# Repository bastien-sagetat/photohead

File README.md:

# Photohead

Photohead is a motorized pan and tilt head on which a camera can be mounted.\

## Initial Concept

## Assembly

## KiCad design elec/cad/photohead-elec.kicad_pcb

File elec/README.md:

# Photohead electronics

The Photohead board aims to drive the stepper motors from PWM signals coming from the Raspberry Pi 5.

To achieve this, two TMC2208 stepper motor drive chips drive two NEMA 17 stepper motors (one for tilting, and one for panning).

🚧: **TODO**: Update overview to show +12V and 3.3V power supplies, GND, and DIR.

**KiCad v8.0 is used throughout this project.**

## Schematic

## Naked board

## Assembled board

## Some therorical stuffs

With microstepping enabled (1/16 microsteps on the TMC2208 chip), and with a step angle of 1.8° on NEMA 17 motors:\
Periods per revolution = (360° / (1.8° / 16)) = 3200 periods\
:arrow_right: 3200 PWM periods are required for the motor to make 1 complete revolution.

If the PWM period is 1 millisecond:\
Full revolution time  = 3200 x 1ms = 3.2s\
:arrow_right: The motor would complete a full revolution in 3.2 seconds.

🚧: **TODO**: Explain Vref calculation.

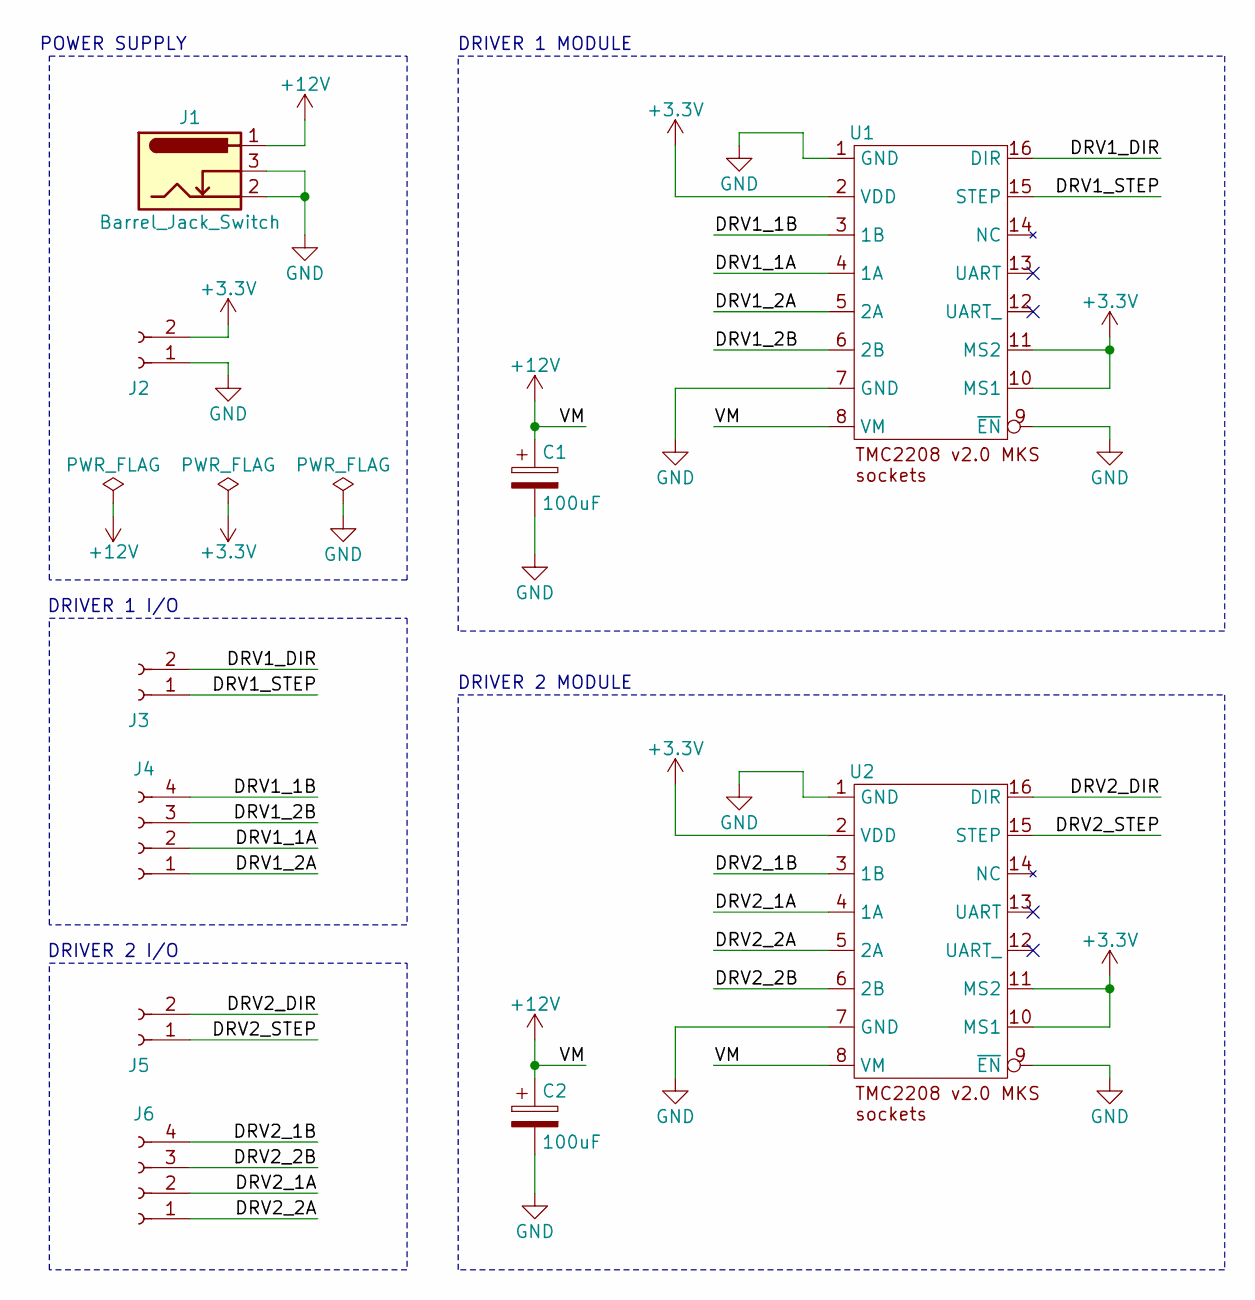
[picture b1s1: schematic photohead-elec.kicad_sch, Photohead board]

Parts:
C1, C2: 100uF
J1: Barrel_Jack_Switch; BarrelJack_Horizontal
J2, J3, J5: Conn_01x02_Socket; PinHeader_1x02_P2.54mm_Vertical
J4, J6: Conn_01x04_Socket; PinHeader_1x04_P2.54mm_Vertical
U1, U2: TMC2208_v2.0_MKS_sockets

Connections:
+3.3V: J2.2, U1.2 (VDD), U1.10 (MS1), U1.11 (MS2), U2.2 (VDD), U2.10 (MS1), U2.11 (MS2)
+12V: C1.1, C2.1, J1.1, U1.8 (VM), U2.8 (VM)
/DRV1_1A: J4.2, U1.4 (1A)
/DRV1_1B: J4.4, U1.3 (1B)
/DRV1_2A: J4.1, U1.5 (2A)
/DRV1_2B: J4.3, U1.6 (2B)
/DRV1_DIR: J3.2, U1.16 (DIR)
/DRV1_STEP: J3.1, U1.15 (STEP)
/DRV2_1A: J6.2, U2.4 (1A)
/DRV2_1B: J6.4, U2.3 (1B)
/DRV2_2A: J6.1, U2.5 (2A)
/DRV2_2B: J6.3, U2.6 (2B)
/DRV2_DIR: J5.2, U2.16 (DIR)
/DRV2_STEP: J5.1, U2.15 (STEP)
GND: C1.2, C2.2, J1.2, J1.3, J2.1, U1.1 (GND), U1.7 (GND), U1.9 (~EN), U2.1 (GND), U2.7 (GND), U2.9 (~EN)

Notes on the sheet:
DRIVER 1 MODULE
POWER SUPPLY
DRIVER 2 I/O
DRIVER 2 MODULE
DRIVER 1 I/O

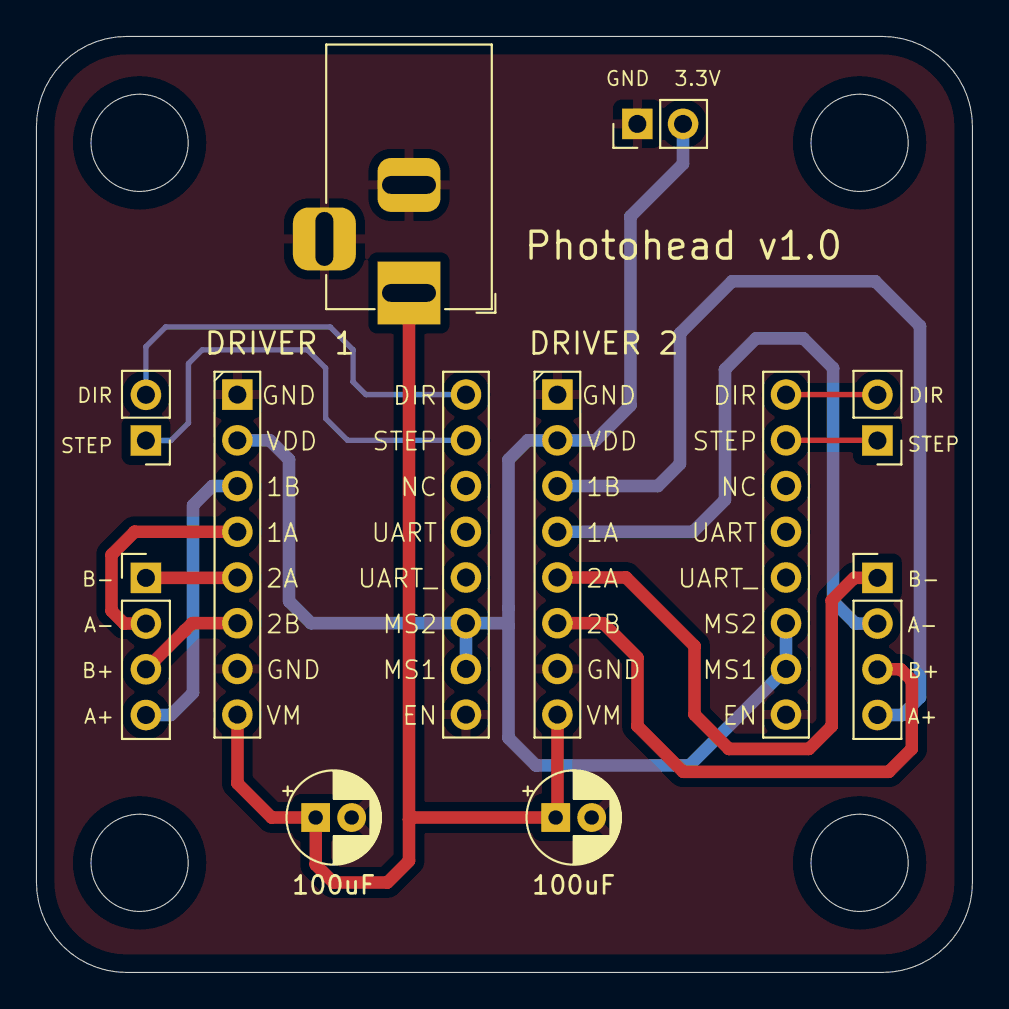
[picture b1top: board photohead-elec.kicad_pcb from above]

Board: 2 copper layers, 52.0 x 52.0 mm, 10 parts (0 on the bottom side), 15 nets.

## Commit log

2023-12-05 Add basic Makefile, main.c, and .gitignore files
2023-12-10 Integrate basic libgphoto2 functions (camera initialization, summary, preview) directly in main.c
2023-12-22 Add camera::File::Mime(), Data() and Size() functions
2023-12-22 Added OpenCV library dependencies
2023-12-22 Convert Camera::File to cv::Mat, and display image in OpenCV window
2023-12-30 Remove Makefile
2023-12-30 Move .h files to src/ folder
2023-12-30 Update main.cpp: remove version infos printing for now
2023-12-30 Update CMakeLists.txt: Link OpenCV library
2023-12-30 Add CMakeLists.txt file
2023-12-30 Update CMakeLists.txt: Link gphoto2 library
2023-12-30 Update CMakeLists.txt: Add compile options/flags
2023-12-30 Add project version printing using CMake template file
2023-12-31 Update CMakeLists.txt: add tensorflow-lite library
2024-01-01 Add model (MobileNetv1-SSD) and model's labels (COCO)
2024-01-01 Update CMakeLists.txt: Copy model and model's labels to build directory
2024-01-01 Integrate object detection directly into main.c (kind of messy but just need a basic integration for now)
2024-01-03 Move model and model's labels to new model/ folder
2024-01-03 Small fix in camera.h
2024-01-06 Add object_detection.cpp/.h source files, and integrate its classes into main.c
2024-01-10 Rework/simplify camera exception
2024-01-10 Add ObjectDetectionException + cosmetics (comments)
2024-01-10 Add PROJECT_NAME to config.h.in template file
2024-01-10 Small ObjectDetector update (score_threshold)
2024-01-10 Update CMakeLists.txt: add comments (cosmetics only)
2024-01-10 Perform continuous image acquisition/processing in while loop
2024-02-02 Rename project (object-detection->owleye)
2024-02-18 Update CMakeLists.txt
    Change required Cmake version
2024-02-24 Add lots of documentation. Rename project
2024-02-26 Apply opaque white background to PNG files
2024-02-26 Resize demo.gif
2024-03-13 Move repository from organization to local repo
2024-03-27 Fix platform - shift the motor downwards - reduce stepper motor bay
2024-03-27 Add platform STL file
2024-04-06 Add tilt head outer bracket FreeCAD file
2024-04-06 Update head outer bracket FreeCAD file
2024-04-06 Add head inner side bracket FreeCAD file
2024-04-06 Add head inner side bracket STL file
2024-04-06 Update head inner side bracket FreeCAD file
2024-04-06 Add head outer bracket STL file
2024-04-06 Add camera mount
2024-04-07 Update README.md: add assembly photo
2024-04-08 Update inner side bracket: remove fillet (was difficult to 3D print)
2024-04-08 Update inner side bracket: remove middle screw holes (2 holes is enough)
2024-04-08 Update inner side bracket: tap the screw holes.
2024-04-08 Update inner side bracket: export STL file
2024-04-09 Update inner side bracket: increase wedge thickness (6mm->8mm)
2024-05-08 Resize camera mount (width set to 134mm)
2024-05-08 Fix typo in config.h.in
2024-05-08 Fix typo in comment
2024-05-08 remove "DLSR" term. Does not have to be a DLSR camera
2024-05-08 Add PWM subproject
2024-05-08 Update requirements.md: Updating "Enabling PWM"
2024-05-08 Update .gitignore (ignore all config.h files)
2026-05-24 REBOOT - Just keeps 3D CAD
    Remove C++ code
    Will use Python app instead
    Remove elec board
    Will use stepper-impulse project instead
2026-05-25 software: bridge: Add blank bridge.py
2026-05-25 software: bridge: Add header to bridge.py
2026-05-25 software: bridge: Basic server
2026-05-25 software: bridge: Add "scan" message type to server
2026-05-26 software: bridge: Add SerialClient and Request classes
2026-06-07 software: bridge: Add bridge script (websocket server)
    Provide a network bridge (websocket),
    to access stepper motor controller (serial communication) remotly:
    Remote user interface (Client) <-> Bridge (Server) <-> stepper controller

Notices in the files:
elec/cad/photohead-elec.kicad_pcb:
creativecommons.org/licenses/by/4.0
License: CC BY 4.0
